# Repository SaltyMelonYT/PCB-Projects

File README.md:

# I'm a nerd  
Incase that wasn't obvious haha. Here is a repository of a bunch of PCB's I've made, from a heart lightboard for your lover (It works) to lampnodes that connect to a central server!

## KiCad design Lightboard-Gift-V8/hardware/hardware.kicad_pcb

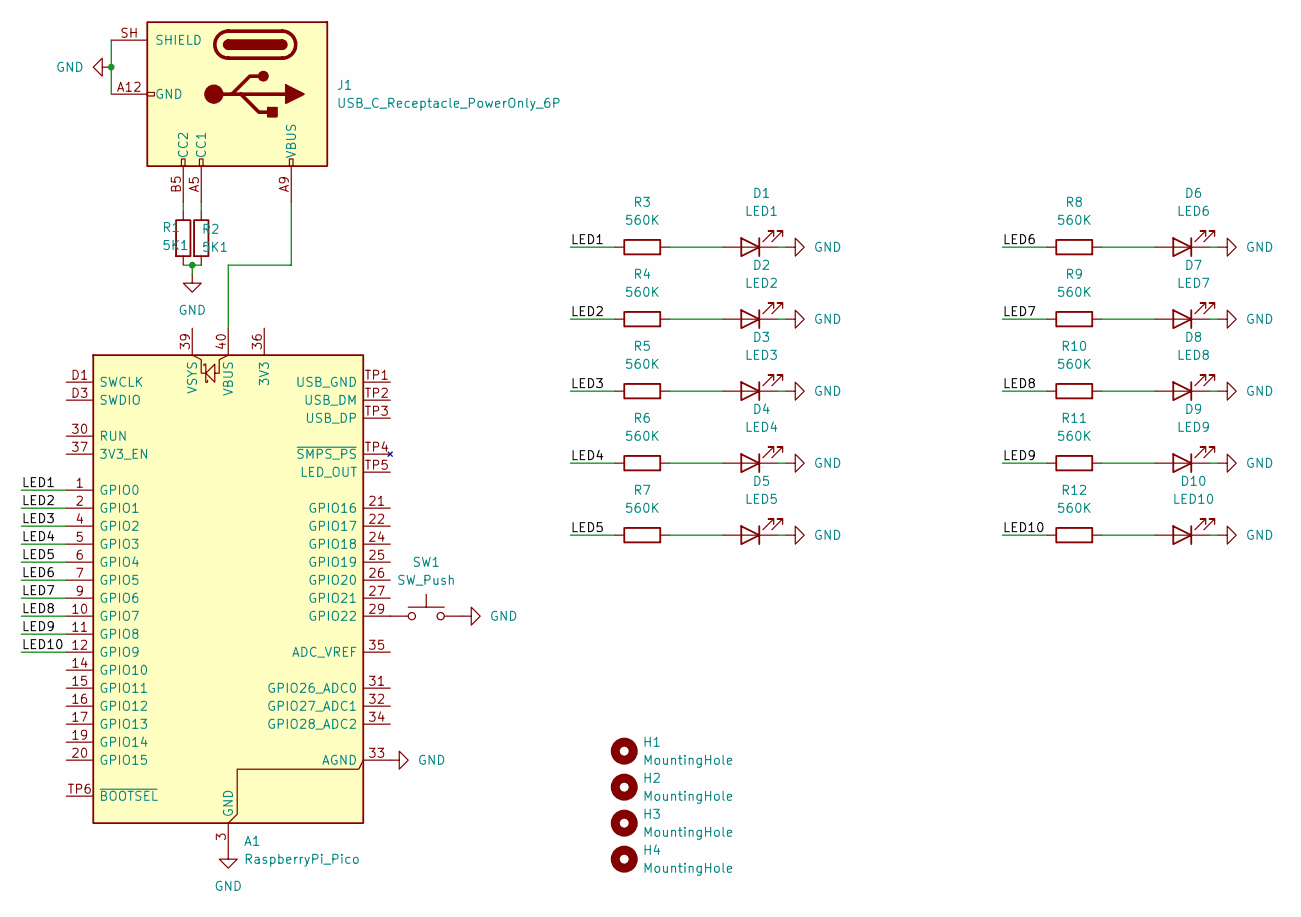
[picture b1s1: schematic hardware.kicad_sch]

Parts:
A1: RaspberryPi_Pico; RaspberryPi_Pico_SMD
D1: LED1; LED_D5.0mm
D2: LED2; LED_D5.0mm
D3: LED3; LED_D5.0mm
D4: LED4; LED_D5.0mm
D5: LED5; LED_D5.0mm
D6: LED6; LED_D5.0mm
D7: LED7; LED_D5.0mm
D8: LED8; LED_D5.0mm
D9: LED9; LED_D5.0mm
D10: LED10; LED_D5.0mm
H1, H2, H3, H4: MountingHole; MountingHole_3.2mm_M3
J1: USB_C_Receptacle_PowerOnly_6P; USB_C_Receptacle_GCT_USB4135-GF-A_6P_TopMnt_Horizontal
R1, R2: 5K1; R_1812_4532Metric
R3, R4, R5, R6, R7, R8, R9, R10, R11, R12: 560K; R_2512_6332Metric
SW1: SW_Push; SW_PUSH_6mm

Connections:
/LED1: A1.1 (GPIO0), R3.1
/LED2: A1.2 (GPIO1), R4.1
/LED3: A1.4 (GPIO2), R5.1
/LED4: A1.5 (GPIO3), R6.1
/LED5: A1.6 (GPIO4), R7.1
/LED6: A1.7 (GPIO5), R8.1
/LED7: A1.9 (GPIO6), R9.1
/LED8: A1.10 (GPIO7), R10.1
/LED9: A1.11 (GPIO8), R11.1
/LED10: A1.12 (GPIO9), R12.1
GND: A1.3 (GND), A1.8 (GND), A1.13 (GND), A1.18 (GND), A1.23 (GND), A1.28 (GND), A1.33 (AGND), A1.38 (GND), A1.D2 (GND), D1.1 (K), D2.1 (K), D3.1 (K), D4.1 (K), D5.1 (K), D6.1 (K), D7.1 (K), D8.1 (K), D9.1 (K), D10.1 (K), J1.A12 (GND), J1.B12 (GND), J1.SH (SHIELD), R1.2, R2.2, SW1.2
unnamed: A1.29 (GPIO22), SW1.1
unnamed: A1.40 (VBUS), J1.A9 (VBUS), J1.B9 (VBUS)
unnamed: D1.2 (A), R3.2
unnamed: D2.2 (A), R4.2
unnamed: D3.2 (A), R5.2
unnamed: D4.2 (A), R6.2
unnamed: D5.2 (A), R7.2
unnamed: D6.2 (A), R8.2
unnamed: D7.2 (A), R9.2
unnamed: D8.2 (A), R10.2
unnamed: D9.2 (A), R11.2
unnamed: D10.2 (A), R12.2
unnamed: J1.A5 (CC1), R1.1
unnamed: J1.B5 (CC2), R2.1

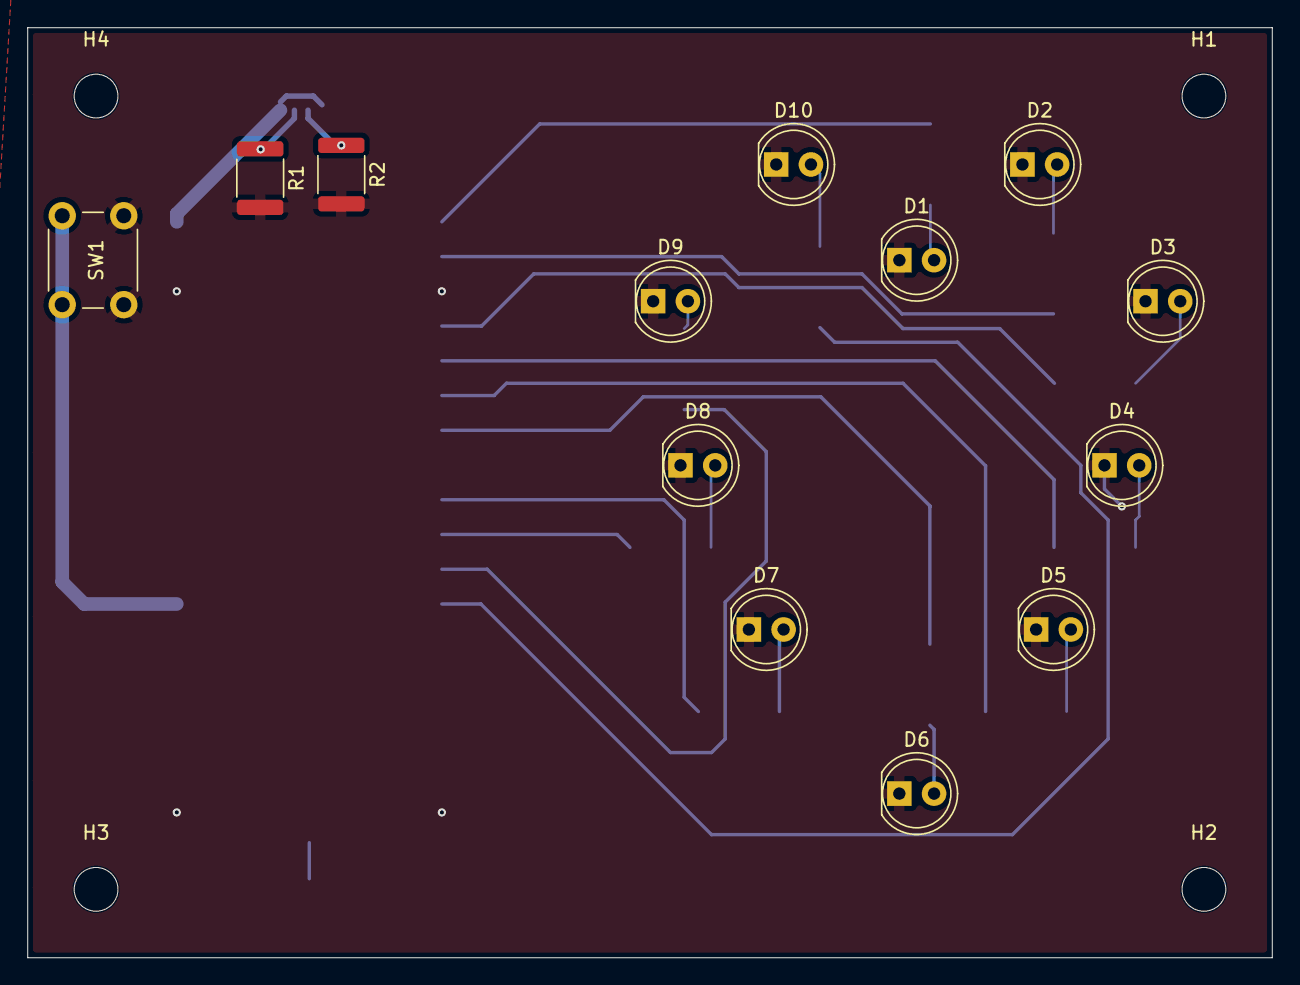
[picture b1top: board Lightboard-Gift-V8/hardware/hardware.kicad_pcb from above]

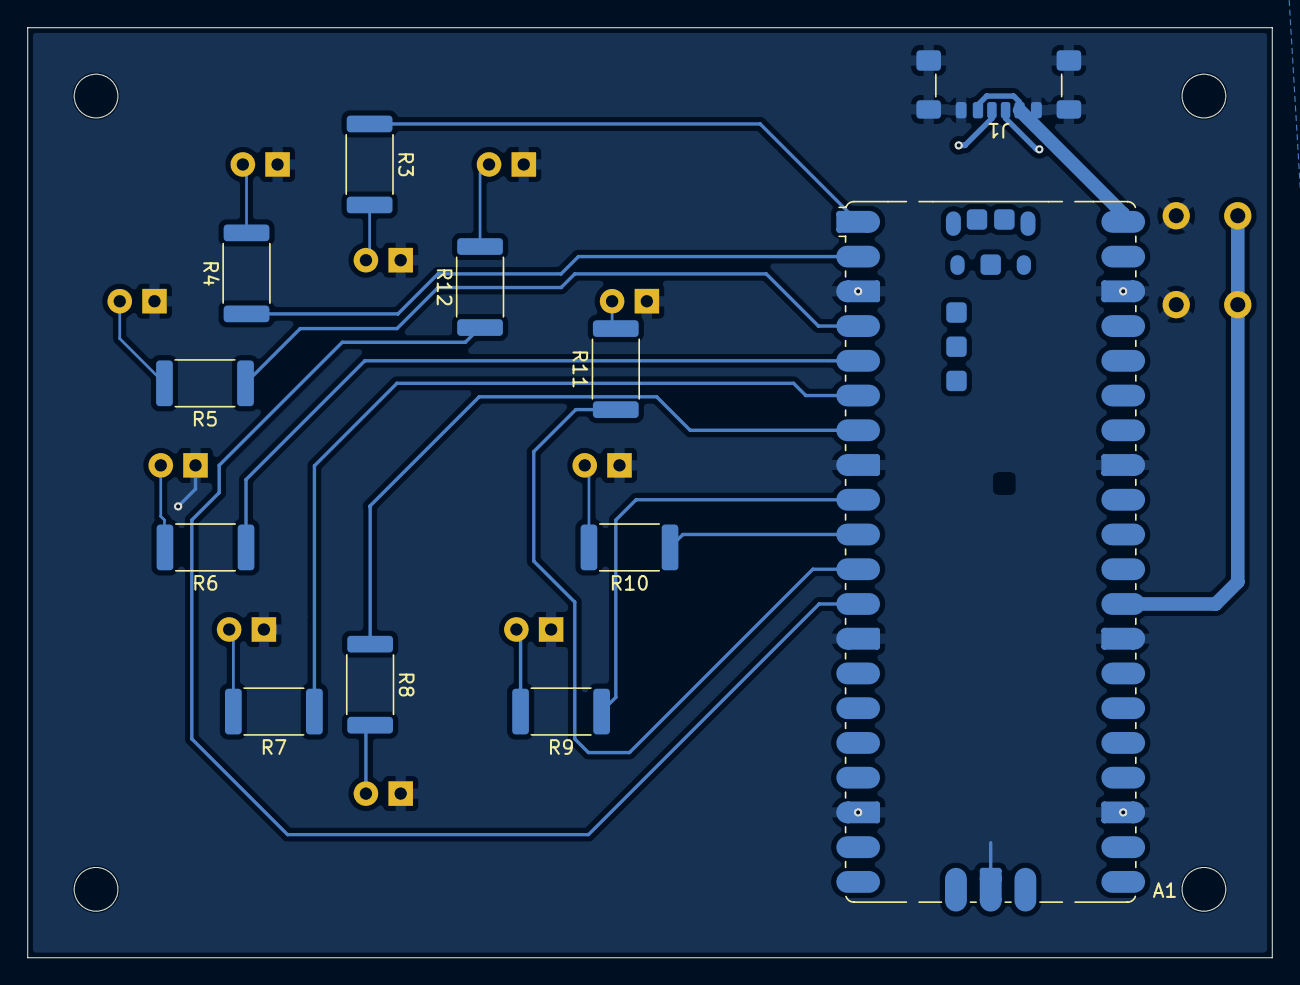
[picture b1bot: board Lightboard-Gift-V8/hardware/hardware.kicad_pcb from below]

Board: 2 copper layers, 91.0 x 68.0 mm, 29 parts (12 on the bottom side), 25 nets.

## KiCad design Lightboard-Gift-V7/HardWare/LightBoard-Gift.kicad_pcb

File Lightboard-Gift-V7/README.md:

## LED Light Board Gift

Tailored towards couples for any occasion, wheather it be Valentines day, Christmas, Birthday, etc

## NEEDED HARDWARE

* One (1) Raspberry Pi Pico
* Ten (10) Chazon 5mm RGB LEDs
* Printed Circuit Board (PCB) from KiCad files
* Ten (10) 560 Ohm 2515 Resistors (220 ohm will work fine, I just chose 560 because it was dimmer without software changes)
* Soldering Iron and solder

## Pictures!!!!

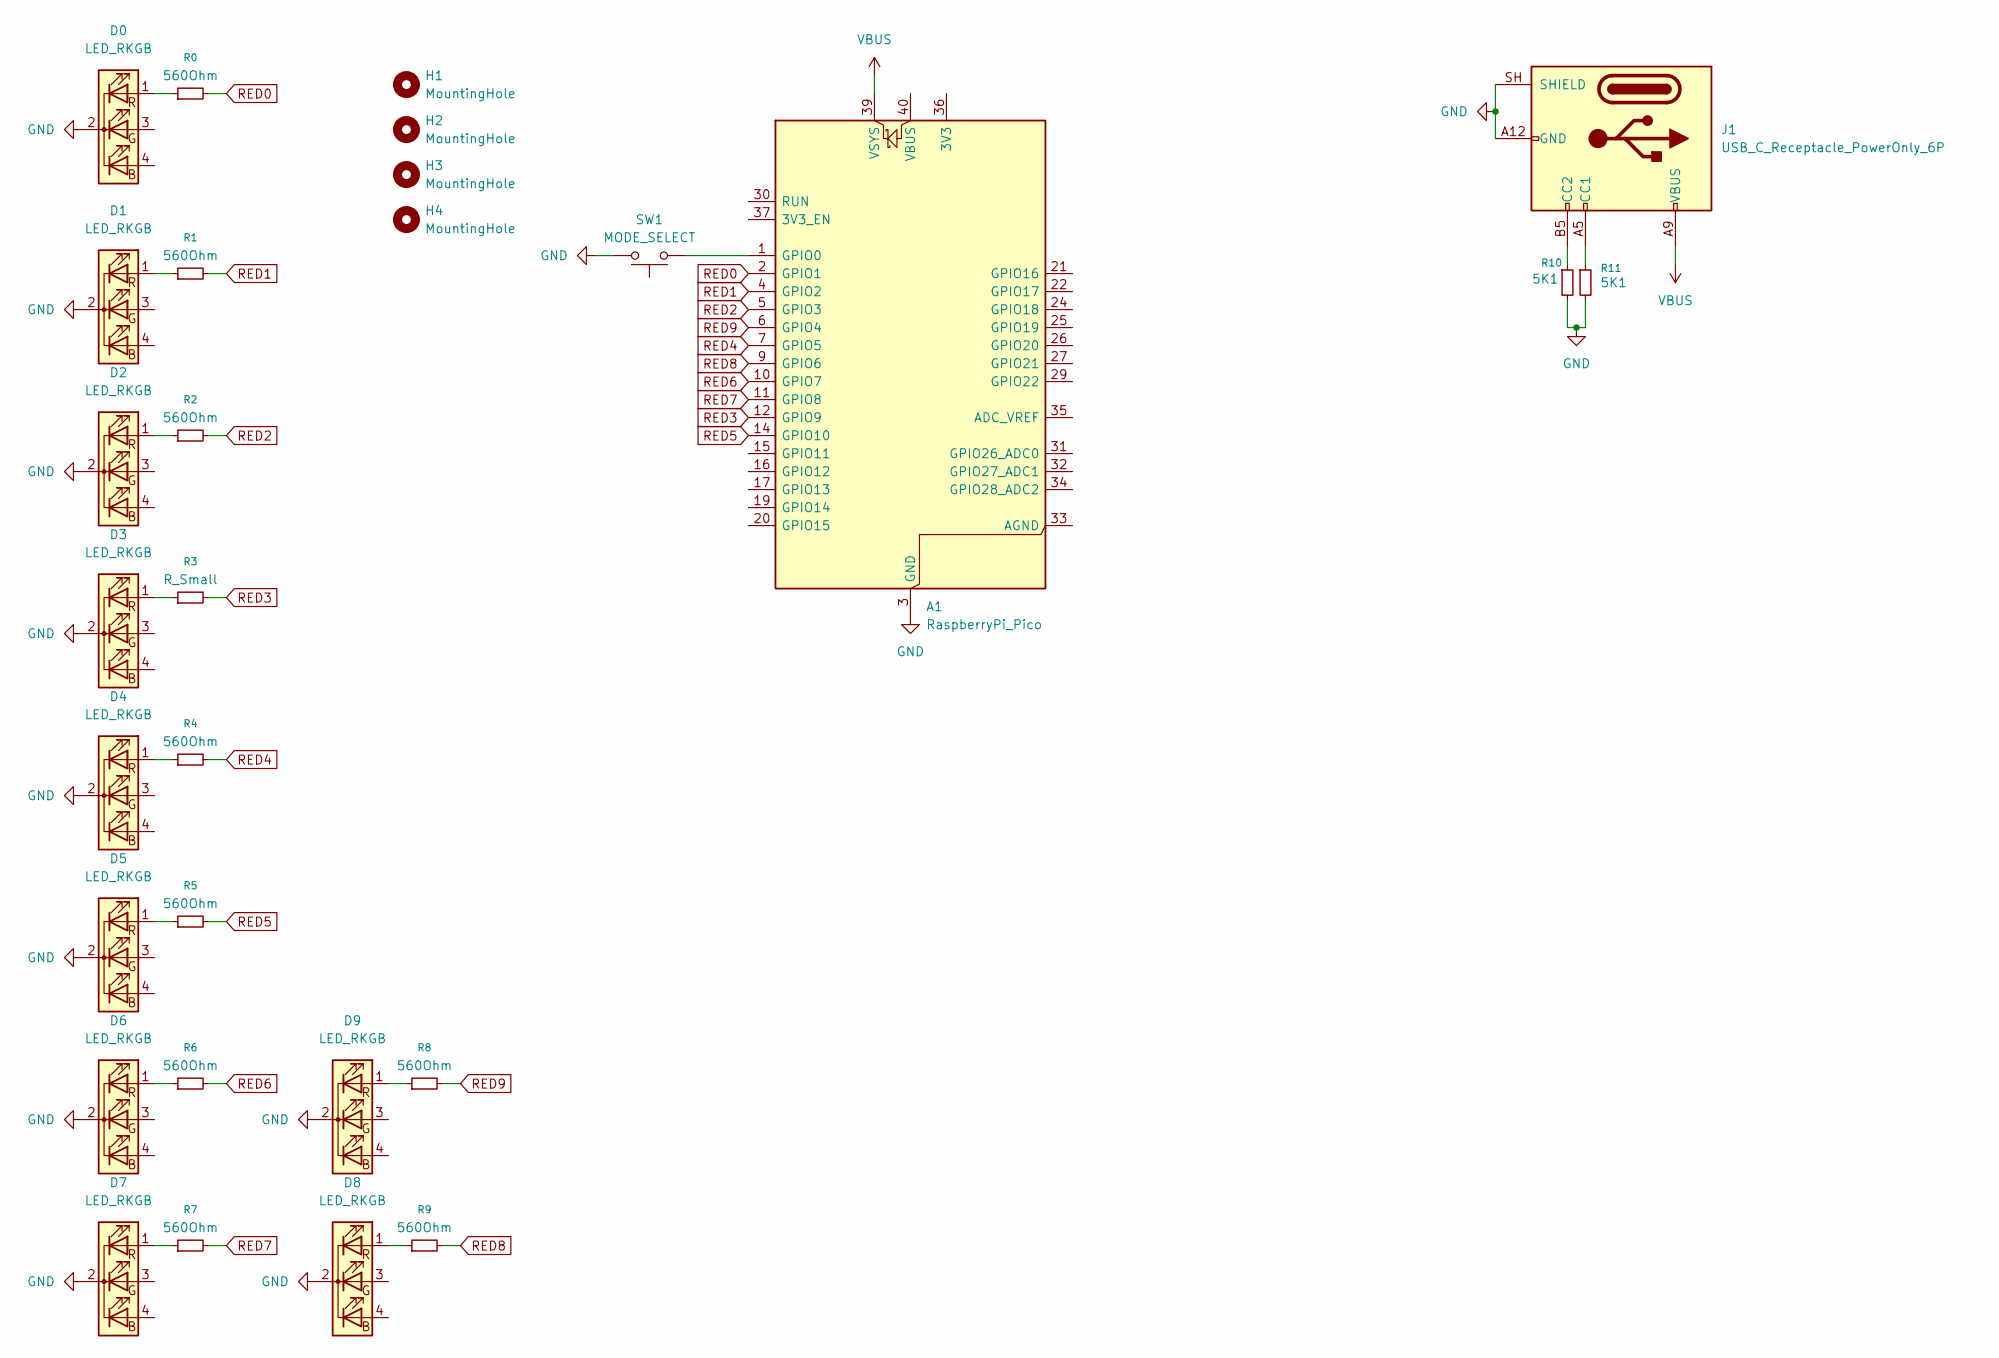
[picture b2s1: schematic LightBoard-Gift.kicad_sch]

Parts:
A1: RaspberryPi_Pico; RaspberryPi_Pico_SMD_HandSolder
D0, D1, D2, D3, D4, D5, D6, D7, D8, D9: LED_RKGB; LED_D5.0mm-4_RGB
H1, H2, H3, H4: MountingHole; MountingHole_3.2mm_M3
J1: USB_C_Receptacle_PowerOnly_6P; USB_C_Receptacle_GCT_USB4125-xx-x_6P_TopMnt_Horizontal
R0, R1, R2, R4, R5, R6, R7, R8, R9: 560Ohm; R_2512_6332Metric
R3: R_Small; R_2512_6332Metric
R10, R11: 5K1; R_2512_6332Metric
SW1: MODE_SELECT; SW_PUSH_6mm_H4.3mm

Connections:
GND: A1.3 (GND), A1.8 (GND), A1.13 (GND), A1.18 (GND), A1.23 (GND), A1.28 (GND), A1.38 (GND), D0.2 (K), D1.2 (K), D2.2 (K), D3.2 (K), D4.2 (K), D5.2 (K), D6.2 (K), D7.2 (K), D8.2 (K), D9.2 (K), J1.A12 (GND), J1.B12 (GND), J1.SH (SHIELD), R10.2, R11.2, SW1.2
unnamed: A1.1 (GPIO0), SW1.1
unnamed: D0.1 (RA), R0.1
unnamed: D1.1 (RA), R1.1
unnamed: D2.1 (RA), R2.1
unnamed: D3.1 (RA), R3.1
unnamed: D4.1 (RA), R4.1
unnamed: D5.1 (RA), R5.1
unnamed: D6.1 (RA), R6.1
unnamed: D7.1 (RA), R7.1
unnamed: D8.1 (RA), R9.1
unnamed: D9.1 (RA), R8.1
unnamed: J1.A5 (CC1), R11.1
unnamed: J1.B5 (CC2), R10.1
RED0: A1.2 (GPIO1), R0.2
RED1: A1.4 (GPIO2), R1.2
RED2: A1.5 (GPIO3), R2.2
RED3: A1.12 (GPIO9), R3.2
RED4: A1.7 (GPIO5), R4.2
RED5: A1.14 (GPIO10), R5.2
RED6: A1.10 (GPIO7), R6.2
RED7: A1.11 (GPIO8), R7.2
RED8: A1.9 (GPIO6), R9.2
RED9: A1.6 (GPIO4), R8.2
VBUS: A1.39 (VSYS), J1.A9 (VBUS), J1.B9 (VBUS)

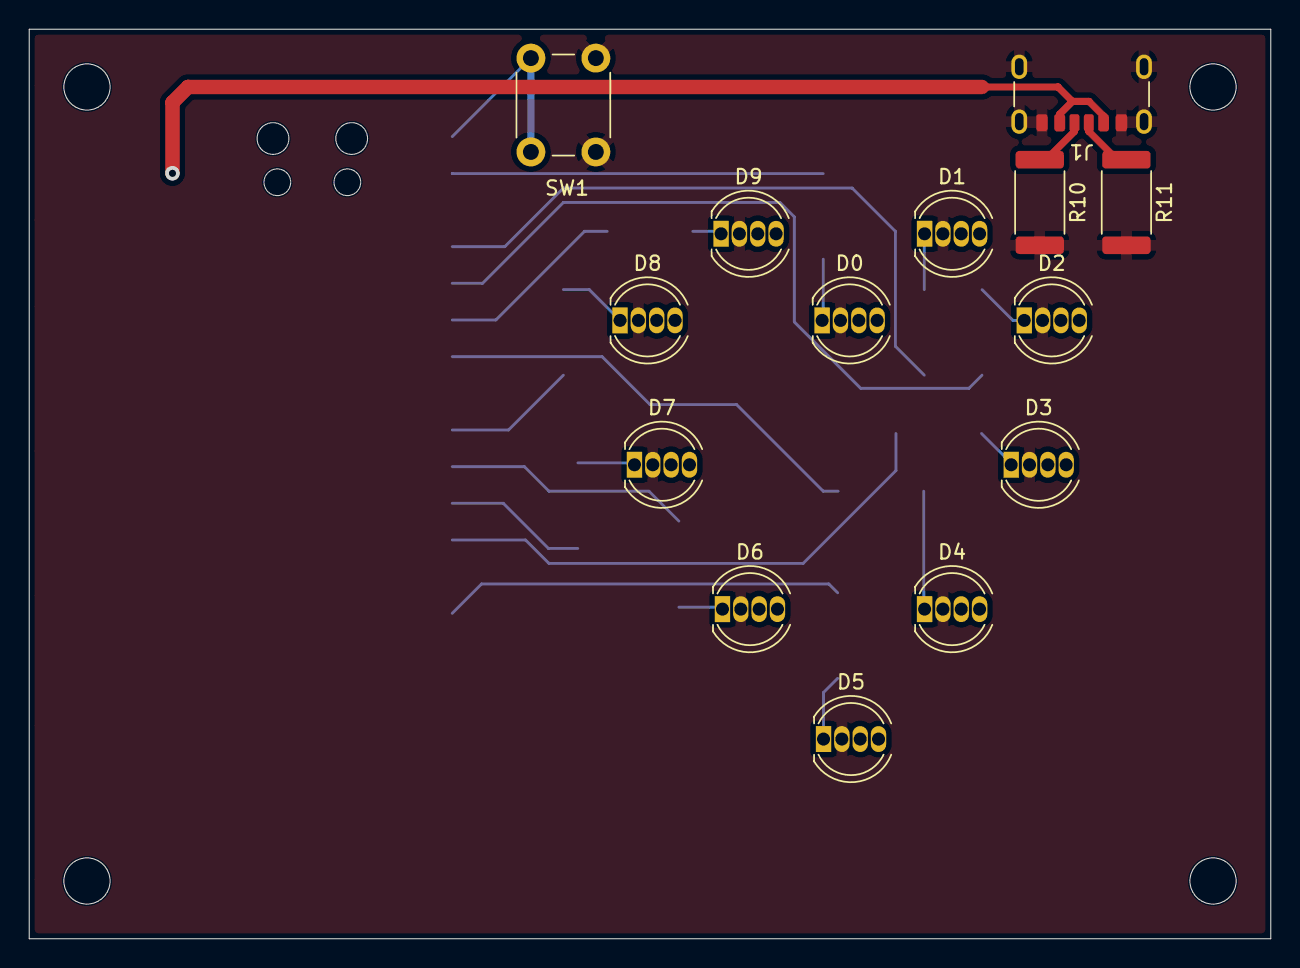
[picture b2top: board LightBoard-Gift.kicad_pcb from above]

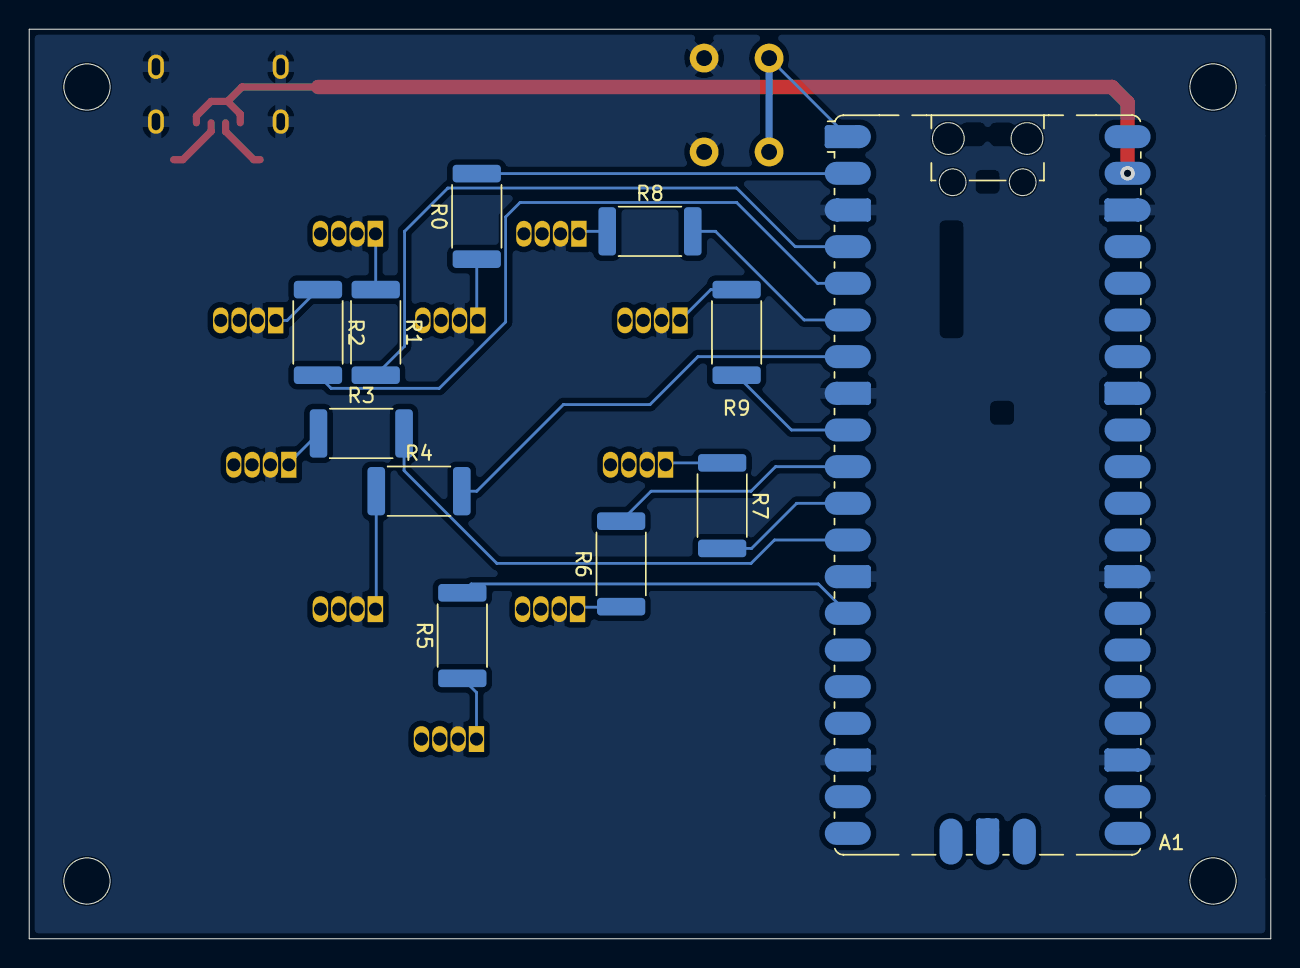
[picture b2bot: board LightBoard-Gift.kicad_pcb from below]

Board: 2 copper layers, 86.0 x 63.0 mm, 29 parts (11 on the bottom side), 25 nets.

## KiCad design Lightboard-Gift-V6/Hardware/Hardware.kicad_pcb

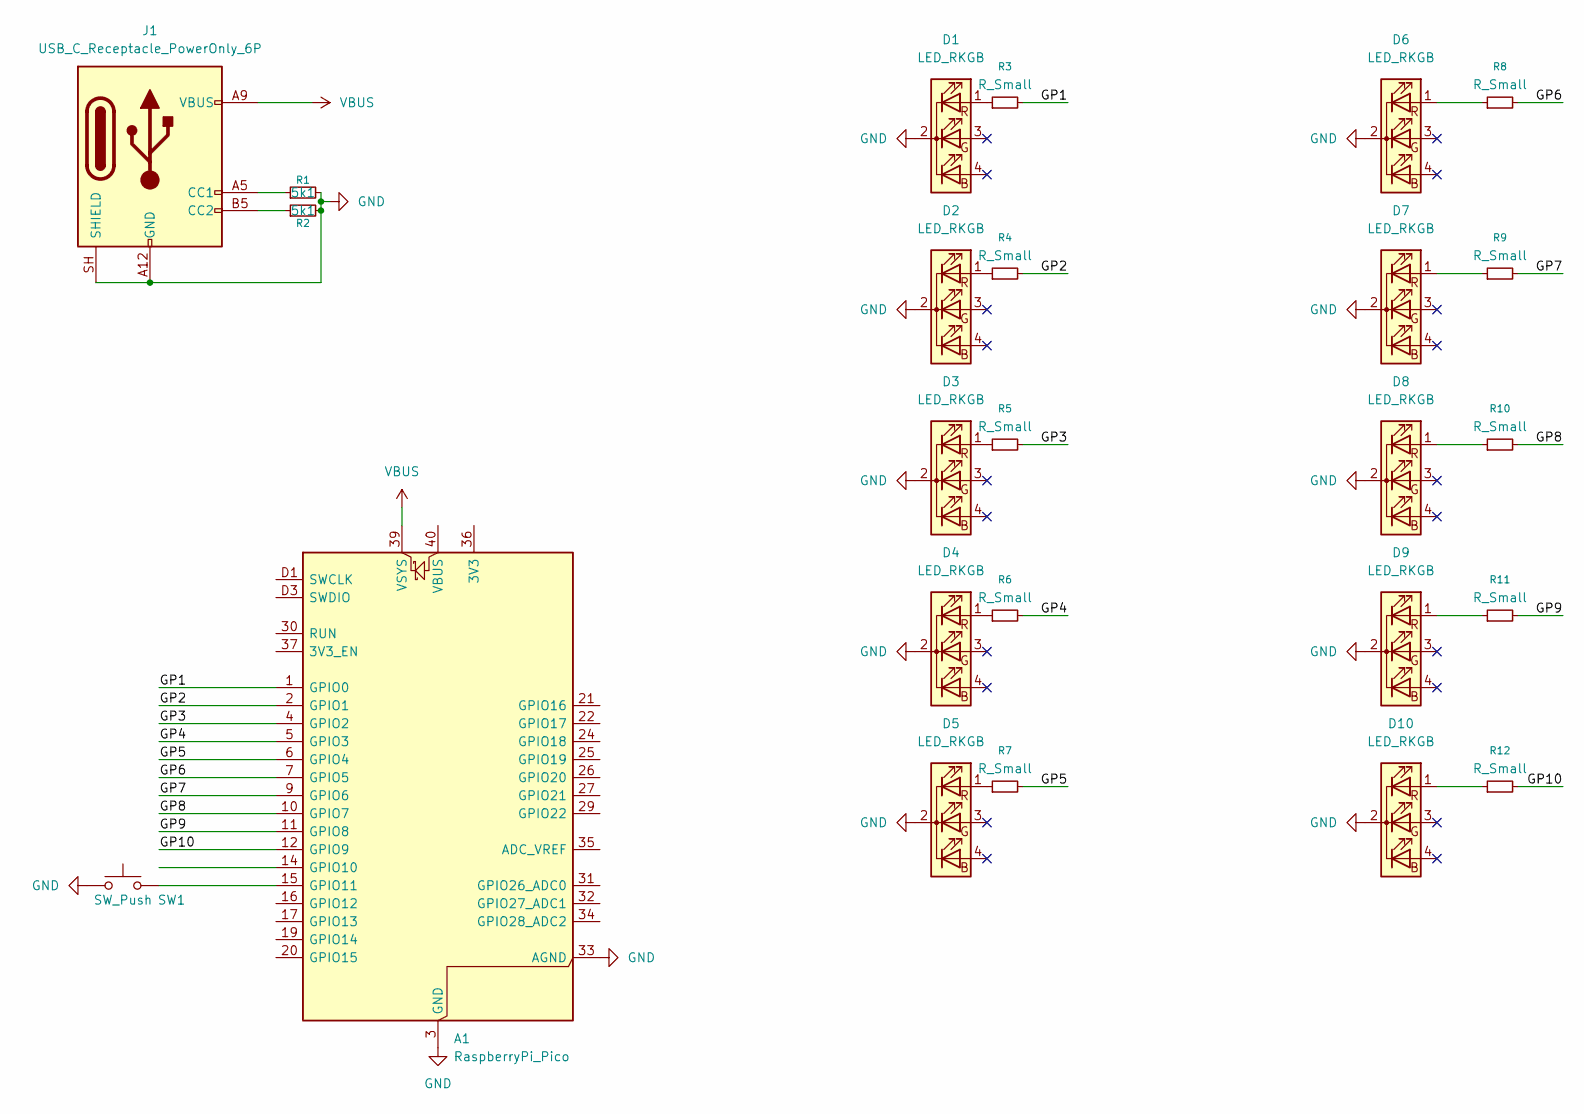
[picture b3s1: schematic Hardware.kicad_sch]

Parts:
A1: RaspberryPi_Pico; RaspberryPi_Pico_SMD_HandSolder
D1, D2, D3, D4, D5, D6, D7, D8, D9, D10: LED_RKGB; LED_D5.0mm-4_RGB
J1: USB_C_Receptacle_PowerOnly_6P; USB_C_Receptacle_GCT_USB4125-xx-x-0190_6P_TopMnt_Horizontal
R1, R2: 5k1; R_2512_6332Metric
R3, R4, R5, R6, R7, R8, R9, R10, R11, R12: R_Small; R_2512_6332Metric
SW1: SW_Push; SW_PUSH_6mm

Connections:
/GP1: A1.1 (GPIO0), R3.2
/GP2: A1.2 (GPIO1), R4.2
/GP3: A1.4 (GPIO2), R5.2
/GP4: A1.5 (GPIO3), R6.2
/GP5: A1.6 (GPIO4), R7.2
/GP6: A1.7 (GPIO5), R8.2
/GP7: A1.9 (GPIO6), R9.2
/GP8: A1.10 (GPIO7), R10.2
/GP9: A1.11 (GPIO8), R11.2
/GP10: A1.12 (GPIO9), R12.2
GND: A1.3 (GND), A1.8 (GND), A1.13 (GND), A1.18 (GND), A1.23 (GND), A1.28 (GND), A1.33 (AGND), A1.38 (GND), A1.D2 (GND), D1.2 (K), D2.2 (K), D3.2 (K), D4.2 (K), D5.2 (K), D6.2 (K), D7.2 (K), D8.2 (K), D9.2 (K), D10.2 (K), J1.A12 (GND), J1.B12 (GND), J1.SH (SHIELD), R1.2, R2.2, SW1.1
unnamed: A1.15 (GPIO11), SW1.2
unnamed: D1.1 (RA), R3.1
unnamed: D2.1 (RA), R4.1
unnamed: D3.1 (RA), R5.1
unnamed: D4.1 (RA), R6.1
unnamed: D5.1 (RA), R7.1
unnamed: D6.1 (RA), R8.1
unnamed: D7.1 (RA), R9.1
unnamed: D8.1 (RA), R10.1
unnamed: D9.1 (RA), R11.1
unnamed: D10.1 (RA), R12.1
unnamed: J1.A5 (CC1), R1.1
unnamed: J1.B5 (CC2), R2.1
VBUS: A1.39 (VSYS), J1.A9 (VBUS), J1.B9 (VBUS)

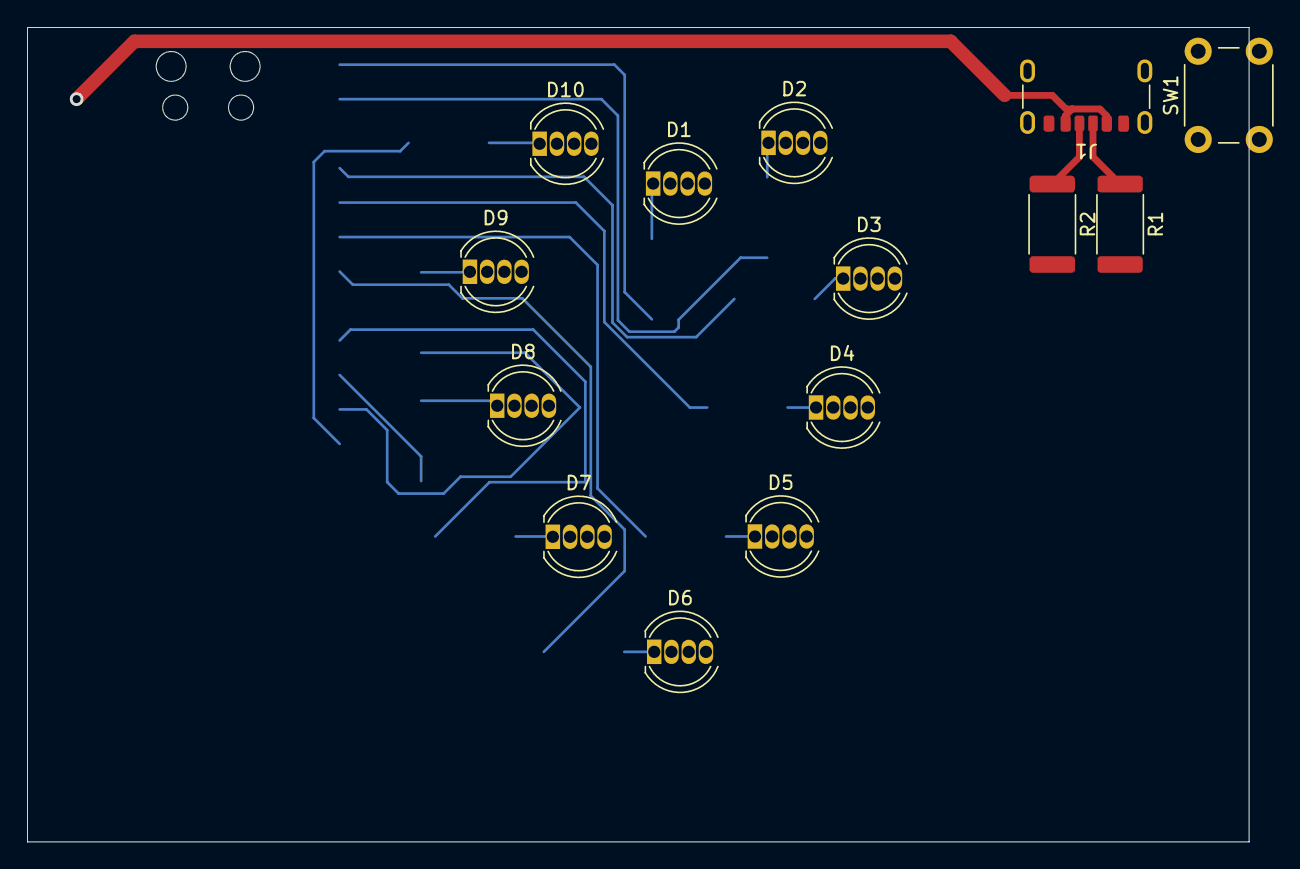
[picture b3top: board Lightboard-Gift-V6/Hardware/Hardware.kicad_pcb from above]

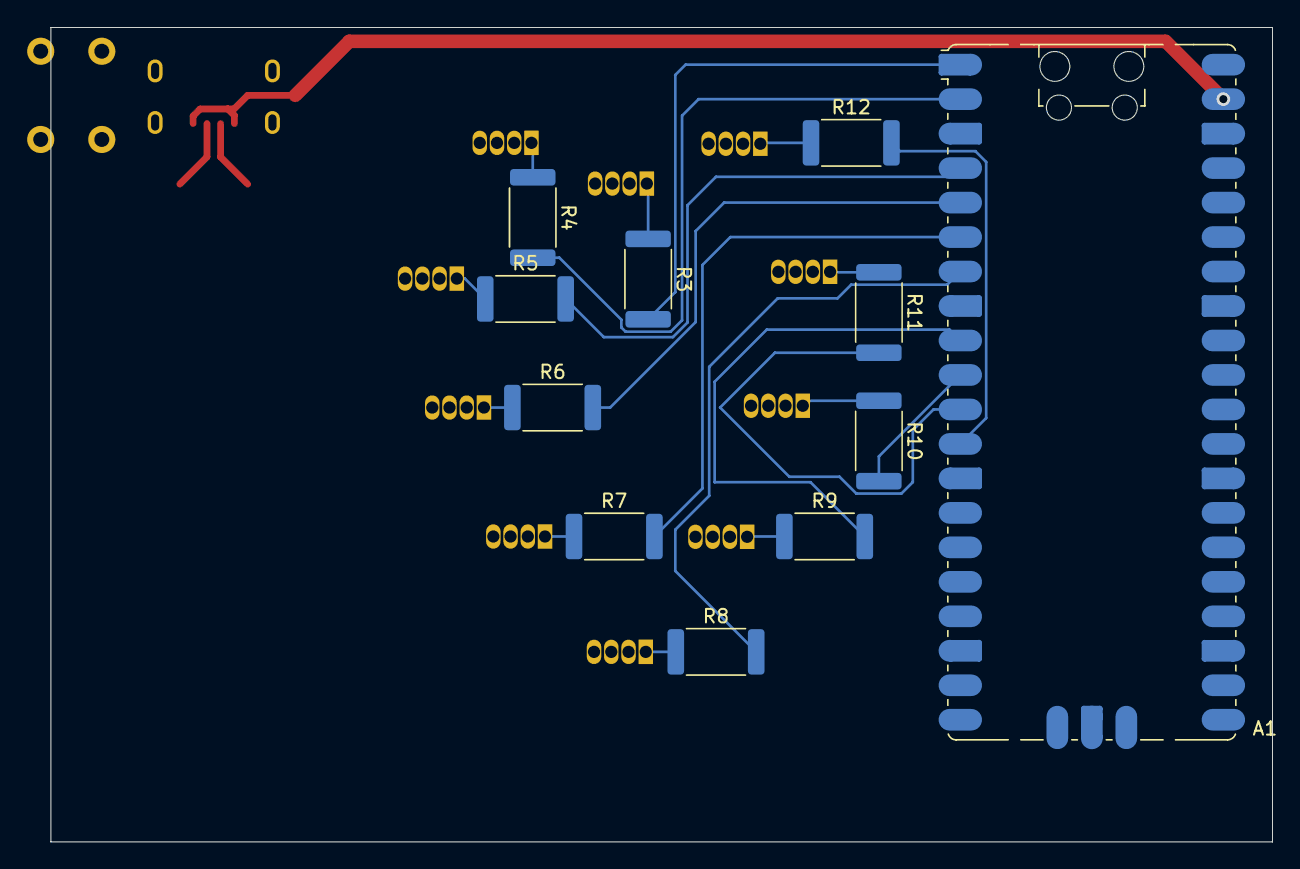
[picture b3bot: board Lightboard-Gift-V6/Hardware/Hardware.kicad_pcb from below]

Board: 2 copper layers, 90.0 x 60.0 mm, 25 parts (11 on the bottom side), 25 nets.

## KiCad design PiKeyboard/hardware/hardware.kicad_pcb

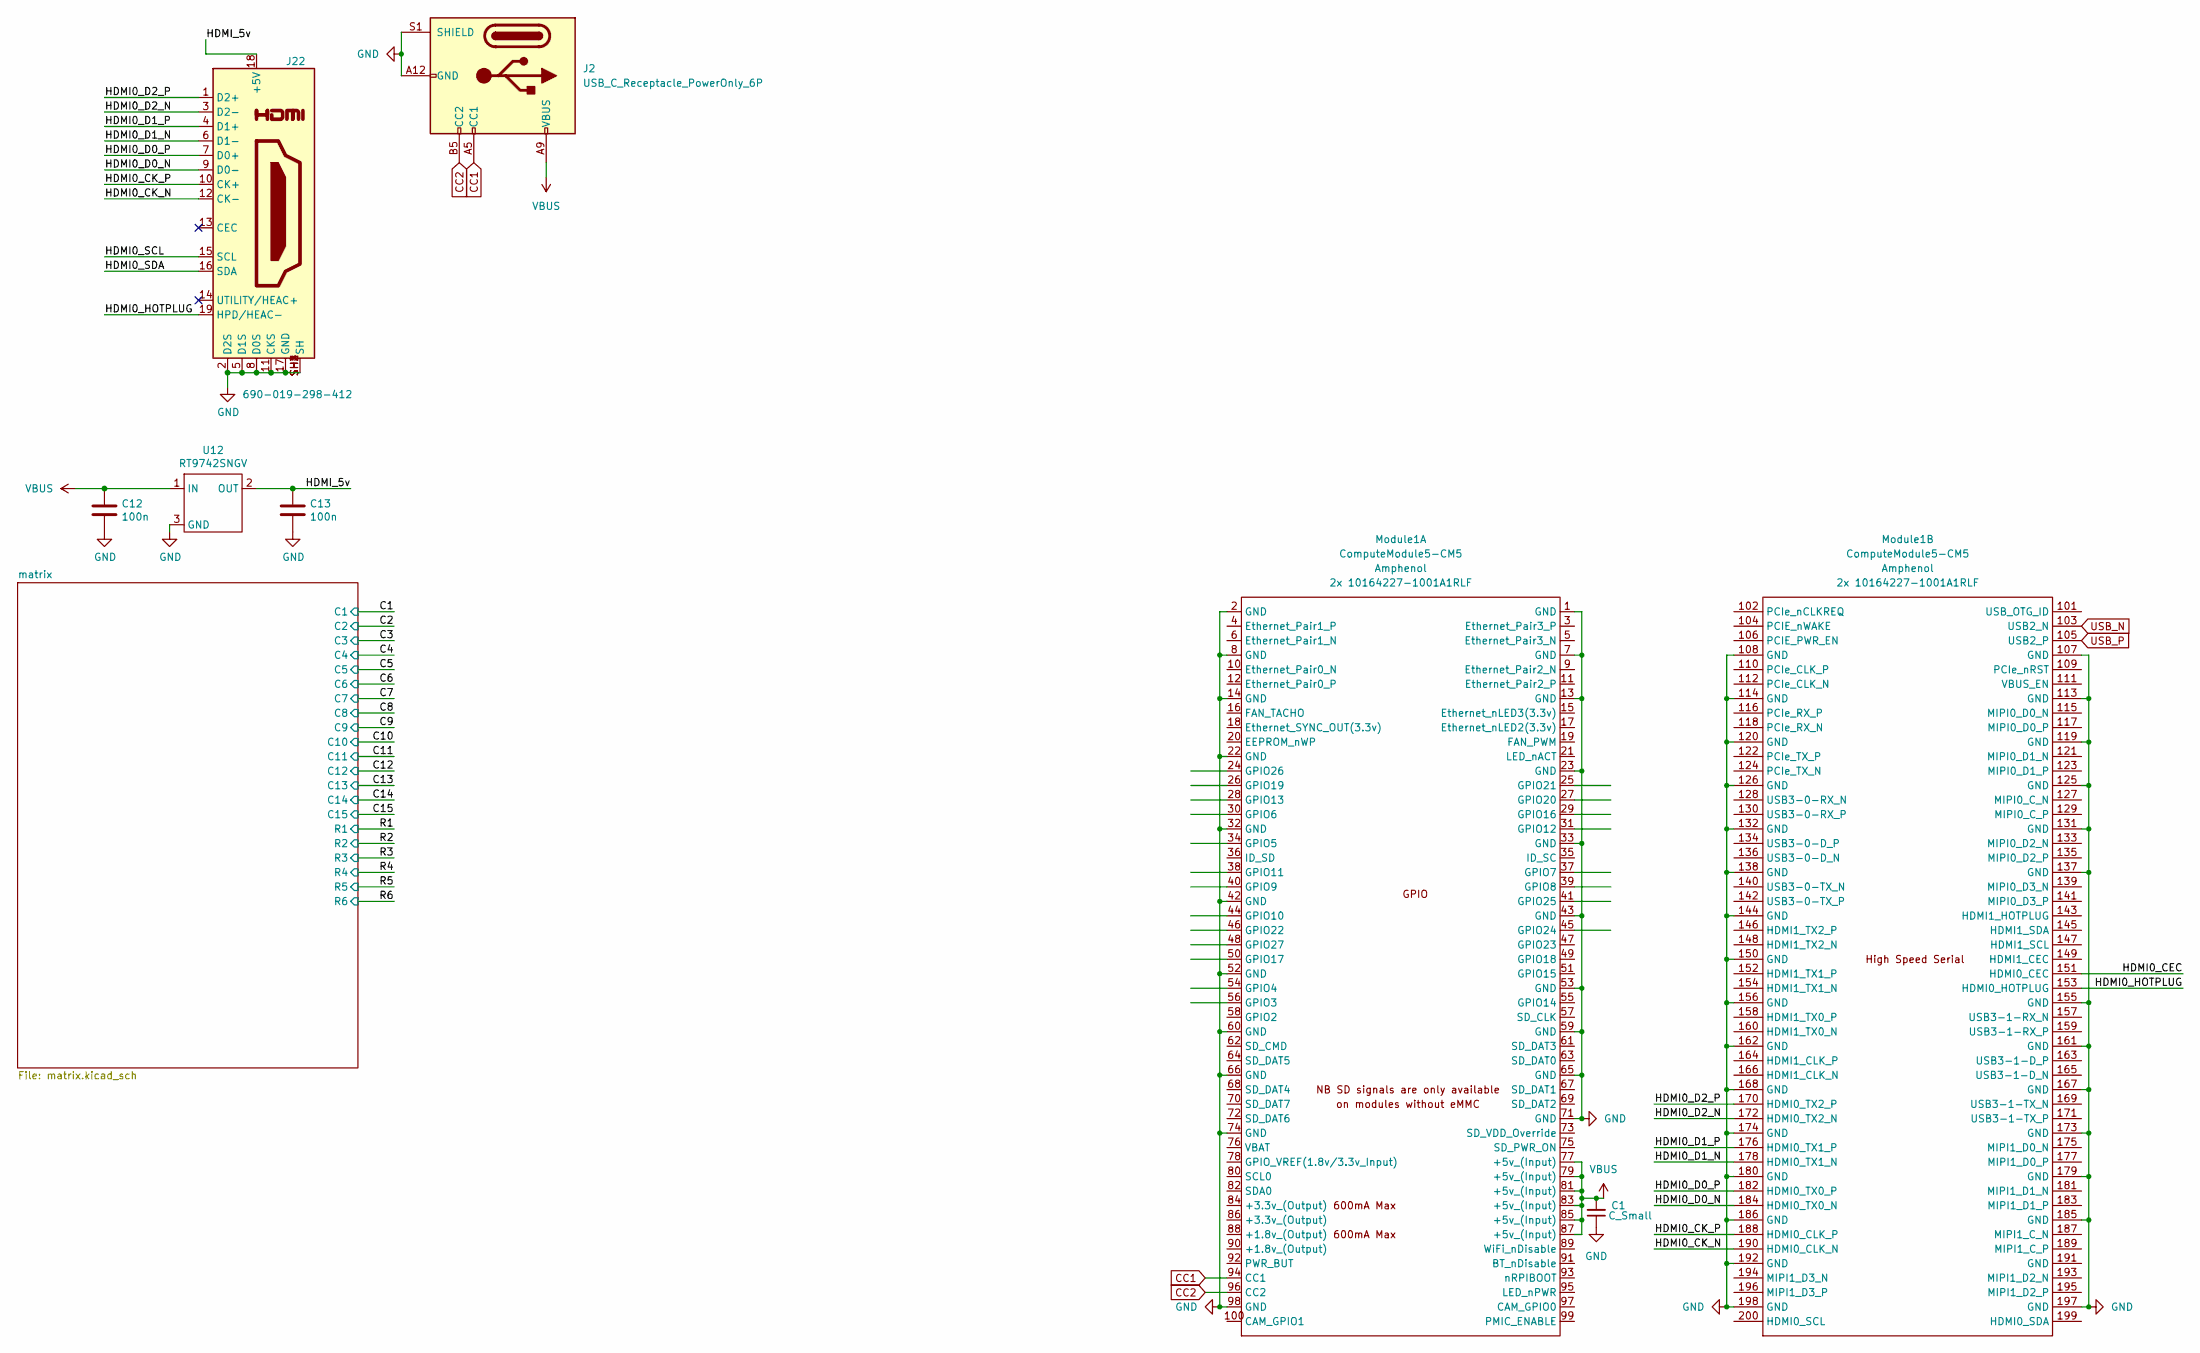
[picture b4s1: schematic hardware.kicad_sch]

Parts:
C1: C_Small; C_0805_2012Metric_Pad1.18x1.45mm_HandSolder
C12, C13: 100n; C_0402_1005Metric; Part Description 0.1uF 10% 16V Ceramic Capacitor X7R 040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
J2: USB_C_Receptacle_PowerOnly_6P; USB_C_Receptacle_GCT_USB4125-xx-x_6P_TopMnt_Horizontal
J22: 690-019-298-412; HDMI_A_Amphenol_10029449-x01xLF_Horizontal; Part Description HDMI Connector, Right Angle, 19 Contact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
Module1: ComputeModule5-CM5; Raspberry-Pi-5-Compute-Module
U12: RT9742SNGV; TSOT-23_HandSoldering; Part Description Power Switch/Driver 1:1 N-Channel 500mA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

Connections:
/HDMI0_CEC: Module1.151 (HDMI0_CEC)
/HDMI0_CK_N: J22.12 (CK-), Module1.190 (HDMI0_CLK_N)
/HDMI0_CK_P: J22.10 (CK+), Module1.188 (HDMI0_CLK_P)
/HDMI0_D0_N: J22.9 (D0-), Module1.184 (HDMI0_TX0_N)
/HDMI0_D0_P: J22.7 (D0+), Module1.182 (HDMI0_TX0_P)
/HDMI0_D1_N: J22.6 (D1-), Module1.178 (HDMI0_TX1_N)
/HDMI0_D1_P: J22.4 (D1+), Module1.176 (HDMI0_TX1_P)
/HDMI0_D2_N: J22.3 (D2-), Module1.172 (HDMI0_TX2_N)
/HDMI0_D2_P: J22.1 (D2+), Module1.170 (HDMI0_TX2_P)
/HDMI0_HOTPLUG: J22.19 (HPD/HEAC-), Module1.153 (HDMI0_HOTPLUG)
/HDMI0_SCL: J22.15 (SCL)
/HDMI0_SDA: J22.16 (SDA)
/HDMI_5v: C13.1, J22.18 (+5V), U12.2 (OUT)
CC1: J2.A5 (CC1), Module1.94 (CC1)
CC2: J2.B5 (CC2), Module1.96 (CC2)
GND: C1.1, C12.2, C13.2, J2.A12 (GND), J2.B12 (GND), J2.S1 (SHIELD), J22.2 (D2S), J22.5 (D1S), J22.8 (D0S), J22.11 (CKS), J22.17 (GND), J22.SH1 (SH), J22.SH2 (SH), J22.SH3 (SH), J22.SH4 (SH), Module1.1 (GND), Module1.2 (GND), Module1.7 (GND), Module1.8 (GND), Module1.13 (GND), Module1.14 (GND), Module1.22 (GND), Module1.23 (GND), Module1.32 (GND), Module1.33 (GND), Module1.42 (GND), Module1.43 (GND), Module1.52 (GND), Module1.53 (GND), Module1.59 (GND), Module1.60 (GND), Module1.65 (GND), Module1.66 (GND), Module1.71 (GND), Module1.74 (GND), Module1.98 (GND), Module1.107 (GND), Module1.108 (GND), Module1.113 (GND), Module1.114 (GND), Module1.119 (GND), Module1.120 (GND), Module1.125 (GND), Module1.126 (GND), Module1.131 (GND), Module1.132 (GND), Module1.137 (GND), Module1.138 (GND), Module1.144 (GND), Module1.150 (GND), Module1.155 (GND), Module1.156 (GND), Module1.161 (GND), Module1.162 (GND), Module1.167 (GND), Module1.168 (GND), Module1.173 (GND), Module1.174 (GND), Module1.179 (GND), Module1.180 (GND), Module1.185 (GND), Module1.186 (GND), Module1.192 (GND), Module1.197 (GND), Module1.198 (GND), U12.3 (GND); also elsewhere on the board
USB_N: Module1.103 (USB2_N); also elsewhere on the board
USB_P: Module1.105 (USB2_P); also elsewhere on the board
VBUS: C1.2, C12.1, J2.A9 (VBUS), J2.B9 (VBUS), Module1.77 (+5v_(Input)), Module1.79 (+5v_(Input)), Module1.81 (+5v_(Input)), Module1.83 (+5v_(Input)), Module1.85 (+5v_(Input)), Module1.87 (+5v_(Input)), U12.1 (IN); also elsewhere on the board
